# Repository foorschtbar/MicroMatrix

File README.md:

#  MicroMatrix

A very tiny 8x8 Pixel LED Matrix (20x20mm) with 64x SK6805-EC15 (1.5x1.5mm) LEDs. With four panels in a chain (8x32 Pixel) perfect for the [PixelIt](https://github.com/o0shojo0o/PixelIt) project.

### PCB Ordering

:point_up: I still have a few PCBs left. If you are interested please contact me. Contact details can be found here: https://github.com/foorschtbar or visit my Tindie store: 

## Layout

```
00 01 02 03 04 05 06 07

15 14 13 12 11 10 09 08

16 17 18 19 20 21 22 23

31 30 29 28 27 26 25 24

32 33 34 35 36 37 38 39

47 46 45 44 43 42 41 40

48 49 50 51 52 53 54 55

63 62 61 60 59 58 57 56
```
## BOM

See [iBOM](./fab/ibom.html)
## Production and Assembly

1. Open KiCad Command Prompt
2. Panelize PCB with [KiKit](https://github.com/yaqwsx/KiKit)

    `kikit panelize -p kikit_panelize.json MicroMatrix.kicad_pcb MicroMatrix_Panel.kicad_pcb`

3. Build fabrication files (Gerber, BOM, POS)

    `kikit fab jlcpcb --no-drc --assembly --field "LCSC Part Number" --schematic MicroMatrix.kicad_sch MicroMatrix_Panel.kicad_pcb fab`

## Other

Inspired by [gumslone/led-matrix](https://oshwlab.com/gumslone/led-matrix).

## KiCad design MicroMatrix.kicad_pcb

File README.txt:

# SK6805EC15 Matrix

https://oshwlab.com/gumslone/led-matrix

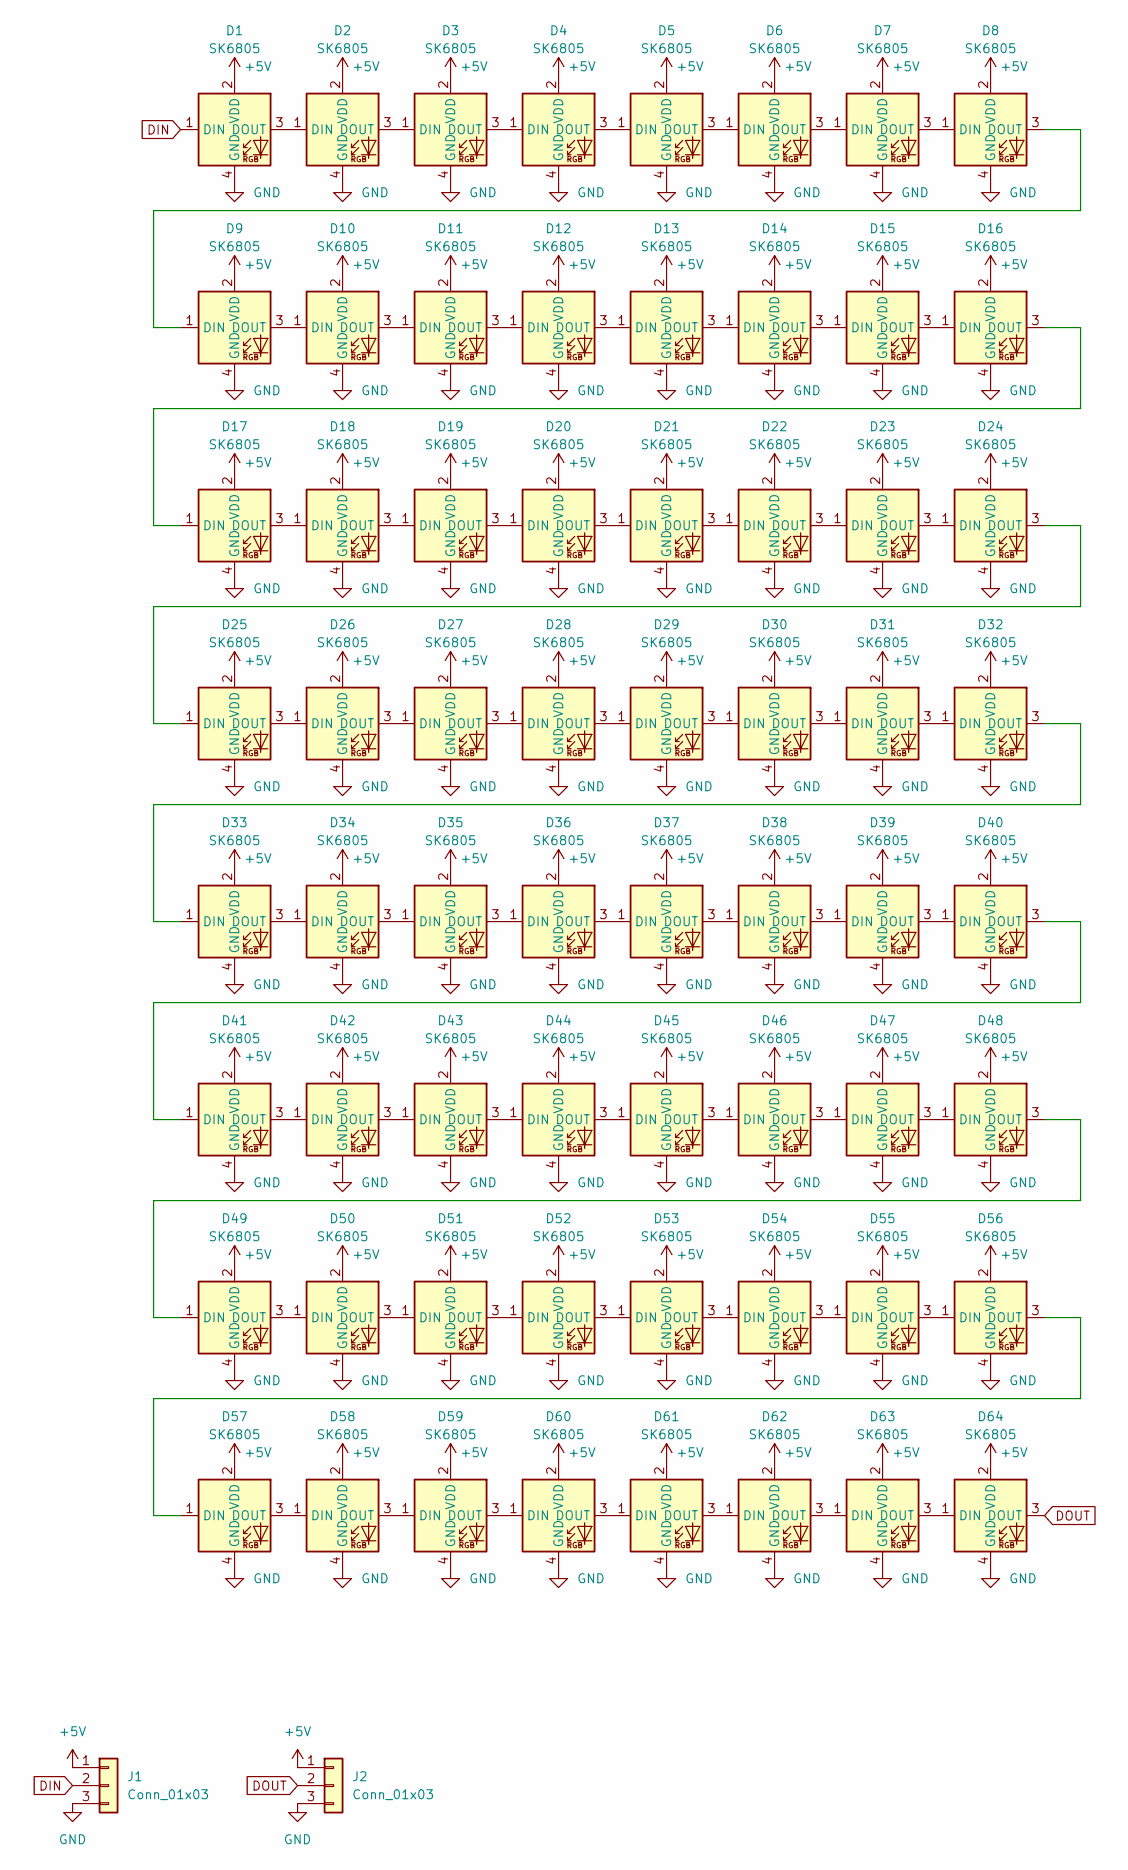
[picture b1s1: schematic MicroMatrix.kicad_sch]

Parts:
D1, D2, D3, D4, D5, D6, D7, D8, D9, D10, D11, D12, D13, D14, D15, D16, D17, D18, D19, D20, D21, D22, D23, D24, D25, D26, D27, D28, D29, D30, D31, D32, D33, D34, D35, D36, D37, D38, D39, D40, D41, D42, D43, D44, D45, D46, D47, D48, D49, D50, D51, D52, D53, D54, D55, D56, D57, D58, D59, D60, D61, D62, D63, D64: SK6805; SK6805-EC15; LCSC Part Number C2890035
J1, J2: Conn_01x03

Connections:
+5V: D1.2 (VDD), D2.2 (VDD), D3.2 (VDD), D4.2 (VDD), D5.2 (VDD), D6.2 (VDD), D7.2 (VDD), D8.2 (VDD), D9.2 (VDD), D10.2 (VDD), D11.2 (VDD), D12.2 (VDD), D13.2 (VDD), D14.2 (VDD), D15.2 (VDD), D16.2 (VDD), D17.2 (VDD), D18.2 (VDD), D19.2 (VDD), D20.2 (VDD), D21.2 (VDD), D22.2 (VDD), D23.2 (VDD), D24.2 (VDD), D25.2 (VDD), D26.2 (VDD), D27.2 (VDD), D28.2 (VDD), D29.2 (VDD), D30.2 (VDD), D31.2 (VDD), D32.2 (VDD), D33.2 (VDD), D34.2 (VDD), D35.2 (VDD), D36.2 (VDD), D37.2 (VDD), D38.2 (VDD), D39.2 (VDD), D40.2 (VDD), D41.2 (VDD), D42.2 (VDD), D43.2 (VDD), D44.2 (VDD), D45.2 (VDD), D46.2 (VDD), D47.2 (VDD), D48.2 (VDD), D49.2 (VDD), D50.2 (VDD), D51.2 (VDD), D52.2 (VDD), D53.2 (VDD), D54.2 (VDD), D55.2 (VDD), D56.2 (VDD), D57.2 (VDD), D58.2 (VDD), D59.2 (VDD), D60.2 (VDD), D61.2 (VDD), D62.2 (VDD), D63.2 (VDD), D64.2 (VDD), J1.1, J2.1
DIN: D1.1 (DIN), J1.2
DOUT: D64.3 (DOUT), J2.2
GND: D1.4 (GND), D2.4 (GND), D3.4 (GND), D4.4 (GND), D5.4 (GND), D6.4 (GND), D7.4 (GND), D8.4 (GND), D9.4 (GND), D10.4 (GND), D11.4 (GND), D12.4 (GND), D13.4 (GND), D14.4 (GND), D15.4 (GND), D16.4 (GND), D17.4 (GND), D18.4 (GND), D19.4 (GND), D20.4 (GND), D21.4 (GND), D22.4 (GND), D23.4 (GND), D24.4 (GND), D25.4 (GND), D26.4 (GND), D27.4 (GND), D28.4 (GND), D29.4 (GND), D30.4 (GND), D31.4 (GND), D32.4 (GND), D33.4 (GND), D34.4 (GND), D35.4 (GND), D36.4 (GND), D37.4 (GND), D38.4 (GND), D39.4 (GND), D40.4 (GND), D41.4 (GND), D42.4 (GND), D43.4 (GND), D44.4 (GND), D45.4 (GND), D46.4 (GND), D47.4 (GND), D48.4 (GND), D49.4 (GND), D50.4 (GND), D51.4 (GND), D52.4 (GND), D53.4 (GND), D54.4 (GND), D55.4 (GND), D56.4 (GND), D57.4 (GND), D58.4 (GND), D59.4 (GND), D60.4 (GND), D61.4 (GND), D62.4 (GND), D63.4 (GND), D64.4 (GND), J1.3, J2.3
unnamed: D1.3 (DOUT), D2.1 (DIN)
unnamed: D2.3 (DOUT), D3.1 (DIN)
unnamed: D3.3 (DOUT), D4.1 (DIN)
unnamed: D4.3 (DOUT), D5.1 (DIN)
unnamed: D5.3 (DOUT), D6.1 (DIN)
unnamed: D6.3 (DOUT), D7.1 (DIN)
unnamed: D7.3 (DOUT), D8.1 (DIN)
unnamed: D8.3 (DOUT), D9.1 (DIN)
unnamed: D9.3 (DOUT), D10.1 (DIN)
unnamed: D10.3 (DOUT), D11.1 (DIN)
unnamed: D11.3 (DOUT), D12.1 (DIN)
unnamed: D12.3 (DOUT), D13.1 (DIN)
unnamed: D13.3 (DOUT), D14.1 (DIN)
unnamed: D14.3 (DOUT), D15.1 (DIN)
unnamed: D15.3 (DOUT), D16.1 (DIN)
unnamed: D16.3 (DOUT), D17.1 (DIN)
unnamed: D17.3 (DOUT), D18.1 (DIN)
unnamed: D18.3 (DOUT), D19.1 (DIN)
unnamed: D19.3 (DOUT), D20.1 (DIN)
unnamed: D20.3 (DOUT), D21.1 (DIN)
unnamed: D21.3 (DOUT), D22.1 (DIN)
unnamed: D22.3 (DOUT), D23.1 (DIN)
unnamed: D23.3 (DOUT), D24.1 (DIN)
unnamed: D24.3 (DOUT), D25.1 (DIN)
unnamed: D25.3 (DOUT), D26.1 (DIN)
unnamed: D26.3 (DOUT), D27.1 (DIN)
unnamed: D27.3 (DOUT), D28.1 (DIN)
unnamed: D28.3 (DOUT), D29.1 (DIN)
unnamed: D29.3 (DOUT), D30.1 (DIN)
unnamed: D30.3 (DOUT), D31.1 (DIN)
unnamed: D31.3 (DOUT), D32.1 (DIN)
unnamed: D32.3 (DOUT), D33.1 (DIN)
unnamed: D33.3 (DOUT), D34.1 (DIN)
unnamed: D34.3 (DOUT), D35.1 (DIN)
unnamed: D35.3 (DOUT), D36.1 (DIN)
unnamed: D36.3 (DOUT), D37.1 (DIN)
unnamed: D37.3 (DOUT), D38.1 (DIN)
unnamed: D38.3 (DOUT), D39.1 (DIN)
unnamed: D39.3 (DOUT), D40.1 (DIN)
unnamed: D40.3 (DOUT), D41.1 (DIN)
unnamed: D41.3 (DOUT), D42.1 (DIN)
unnamed: D42.3 (DOUT), D43.1 (DIN)
unnamed: D43.3 (DOUT), D44.1 (DIN)
unnamed: D44.3 (DOUT), D45.1 (DIN)
unnamed: D45.3 (DOUT), D46.1 (DIN)
unnamed: D46.3 (DOUT), D47.1 (DIN)
unnamed: D47.3 (DOUT), D48.1 (DIN)
unnamed: D48.3 (DOUT), D49.1 (DIN)
unnamed: D49.3 (DOUT), D50.1 (DIN)
unnamed: D50.3 (DOUT), D51.1 (DIN)
unnamed: D51.3 (DOUT), D52.1 (DIN)
unnamed: D52.3 (DOUT), D53.1 (DIN)
unnamed: D53.3 (DOUT), D54.1 (DIN)
unnamed: D54.3 (DOUT), D55.1 (DIN)
unnamed: D55.3 (DOUT), D56.1 (DIN)
unnamed: D56.3 (DOUT), D57.1 (DIN)
unnamed: D57.3 (DOUT), D58.1 (DIN)
unnamed: D58.3 (DOUT), D59.1 (DIN)
unnamed: D59.3 (DOUT), D60.1 (DIN)
unnamed: D60.3 (DOUT), D61.1 (DIN)
unnamed: D61.3 (DOUT), D62.1 (DIN)
unnamed: D62.3 (DOUT), D63.1 (DIN)
unnamed: D63.3 (DOUT), D64.1 (DIN)

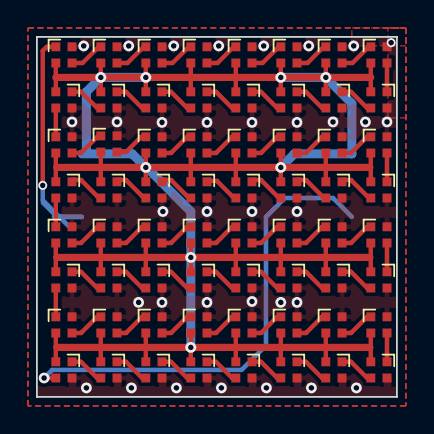
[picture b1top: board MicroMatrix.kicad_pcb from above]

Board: 2 copper layers, 20.0 x 20.0 mm, 64 parts (0 on the bottom side), 65 nets.

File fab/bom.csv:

Comment,Designator,Footprint,LCSC
SK6805,"D1,D2,D3,D4,D5,D6,D7,D8,D9,D10,D11,D12,D13,D14,D15,D16,D17,D18,D19,D20,D21,D22,D23,D24,D25,D26,D27,D28,D29,D30,D31,D32,D33,D34,D35,D36,D37,D38,D39,D40,D41,D42,D43,D44,D45,D46,D47,D48,D49,D50,D51,D52,D53,D54,D55,D56,D57,D58,D59,D60,D61,D62,D63,D64",LED_SMD:LED_SK6812_EC15_1.5x1.5mm,C2890035

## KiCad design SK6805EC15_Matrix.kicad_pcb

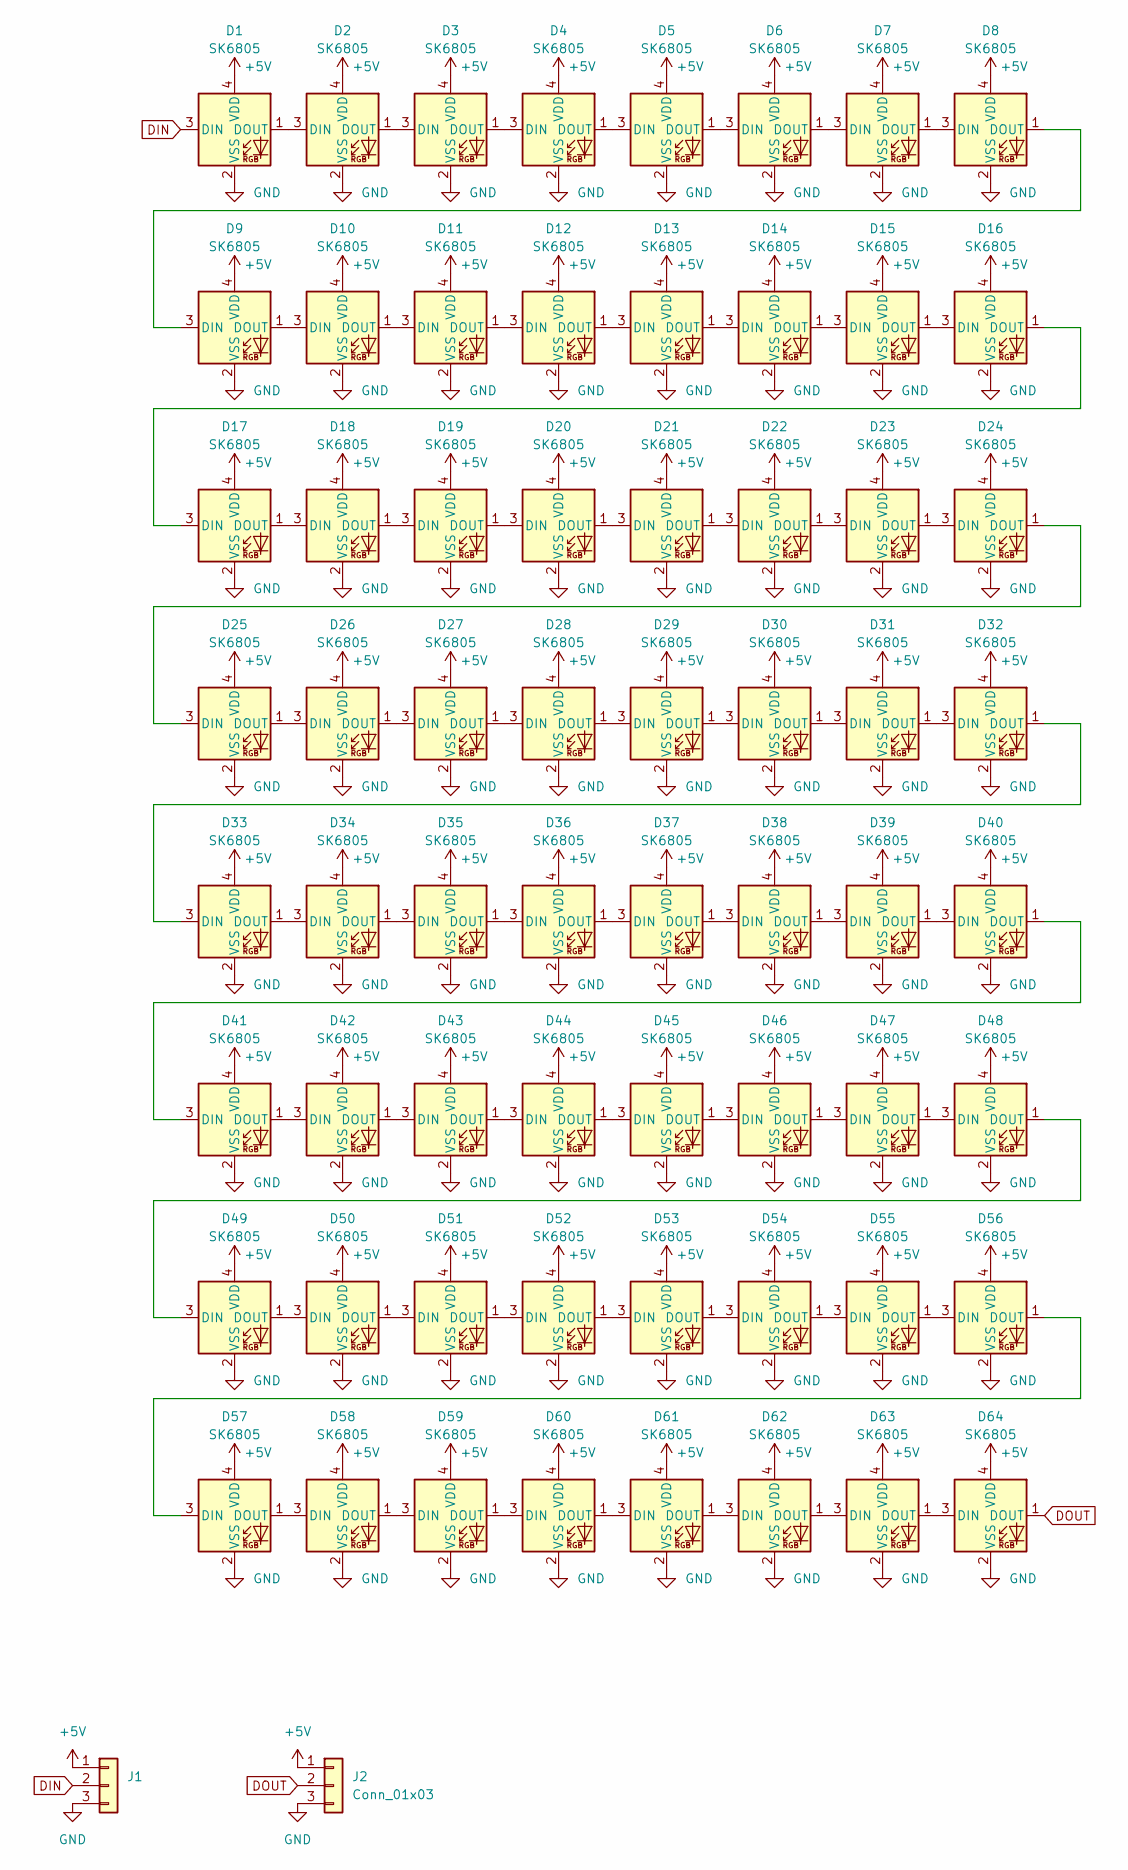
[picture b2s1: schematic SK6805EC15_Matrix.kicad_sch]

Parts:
D1, D2, D3, D4, D5, D6, D7, D8, D9, D10, D11, D12, D13, D14, D15, D16, D17, D18, D19, D20, D21, D22, D23, D24, D25, D26, D27, D28, D29, D30, D31, D32, D33, D34, D35, D36, D37, D38, D39, D40, D41, D42, D43, D44, D45, D46, D47, D48, D49, D50, D51, D52, D53, D54, D55, D56, D57, D58, D59, D60, D61, D62, D63, D64: SK6805; LED_SK6812_EC15_1.5x1.5mm
J1: (no value)
J2: Conn_01x03

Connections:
+5V: D1.4 (VDD), D2.4 (VDD), D3.4 (VDD), D4.4 (VDD), D5.4 (VDD), D6.4 (VDD), D7.4 (VDD), D8.4 (VDD), D9.4 (VDD), D10.4 (VDD), D11.4 (VDD), D12.4 (VDD), D13.4 (VDD), D14.4 (VDD), D15.4 (VDD), D16.4 (VDD), D17.4 (VDD), D18.4 (VDD), D19.4 (VDD), D20.4 (VDD), D21.4 (VDD), D22.4 (VDD), D23.4 (VDD), D24.4 (VDD), D25.4 (VDD), D26.4 (VDD), D27.4 (VDD), D28.4 (VDD), D29.4 (VDD), D30.4 (VDD), D31.4 (VDD), D32.4 (VDD), D33.4 (VDD), D34.4 (VDD), D35.4 (VDD), D36.4 (VDD), D37.4 (VDD), D38.4 (VDD), D39.4 (VDD), D40.4 (VDD), D41.4 (VDD), D42.4 (VDD), D43.4 (VDD), D44.4 (VDD), D45.4 (VDD), D46.4 (VDD), D47.4 (VDD), D48.4 (VDD), D49.4 (VDD), D50.4 (VDD), D51.4 (VDD), D52.4 (VDD), D53.4 (VDD), D54.4 (VDD), D55.4 (VDD), D56.4 (VDD), D57.4 (VDD), D58.4 (VDD), D59.4 (VDD), D60.4 (VDD), D61.4 (VDD), D62.4 (VDD), D63.4 (VDD), D64.4 (VDD), J1.1, J2.1
DIN: D1.3 (DIN), J1.2
DOUT: D64.1 (DOUT), J2.2
GND: D1.2 (VSS), D2.2 (VSS), D3.2 (VSS), D4.2 (VSS), D5.2 (VSS), D6.2 (VSS), D7.2 (VSS), D8.2 (VSS), D9.2 (VSS), D10.2 (VSS), D11.2 (VSS), D12.2 (VSS), D13.2 (VSS), D14.2 (VSS), D15.2 (VSS), D16.2 (VSS), D17.2 (VSS), D18.2 (VSS), D19.2 (VSS), D20.2 (VSS), D21.2 (VSS), D22.2 (VSS), D23.2 (VSS), D24.2 (VSS), D25.2 (VSS), D26.2 (VSS), D27.2 (VSS), D28.2 (VSS), D29.2 (VSS), D30.2 (VSS), D31.2 (VSS), D32.2 (VSS), D33.2 (VSS), D34.2 (VSS), D35.2 (VSS), D36.2 (VSS), D37.2 (VSS), D38.2 (VSS), D39.2 (VSS), D40.2 (VSS), D41.2 (VSS), D42.2 (VSS), D43.2 (VSS), D44.2 (VSS), D45.2 (VSS), D46.2 (VSS), D47.2 (VSS), D48.2 (VSS), D49.2 (VSS), D50.2 (VSS), D51.2 (VSS), D52.2 (VSS), D53.2 (VSS), D54.2 (VSS), D55.2 (VSS), D56.2 (VSS), D57.2 (VSS), D58.2 (VSS), D59.2 (VSS), D60.2 (VSS), D61.2 (VSS), D62.2 (VSS), D63.2 (VSS), D64.2 (VSS), J1.3, J2.3
unnamed: D1.1 (DOUT), D2.3 (DIN)
unnamed: D2.1 (DOUT), D3.3 (DIN)
unnamed: D3.1 (DOUT), D4.3 (DIN)
unnamed: D4.1 (DOUT), D5.3 (DIN)
unnamed: D5.1 (DOUT), D6.3 (DIN)
unnamed: D6.1 (DOUT), D7.3 (DIN)
unnamed: D7.1 (DOUT), D8.3 (DIN)
unnamed: D8.1 (DOUT), D9.3 (DIN)
unnamed: D10.1 (DOUT), D11.3 (DIN)
unnamed: D9.1 (DOUT), D10.3 (DIN)
unnamed: D11.1 (DOUT), D12.3 (DIN)
unnamed: D12.1 (DOUT), D13.3 (DIN)
unnamed: D13.1 (DOUT), D14.3 (DIN)
unnamed: D14.1 (DOUT), D15.3 (DIN)
unnamed: D15.1 (DOUT), D16.3 (DIN)
unnamed: D16.1 (DOUT), D17.3 (DIN)
unnamed: D17.1 (DOUT), D18.3 (DIN)
unnamed: D18.1 (DOUT), D19.3 (DIN)
unnamed: D19.1 (DOUT), D20.3 (DIN)
unnamed: D20.1 (DOUT), D21.3 (DIN)
unnamed: D21.1 (DOUT), D22.3 (DIN)
unnamed: D22.1 (DOUT), D23.3 (DIN)
unnamed: D23.1 (DOUT), D24.3 (DIN)
unnamed: D24.1 (DOUT), D25.3 (DIN)
unnamed: D25.1 (DOUT), D26.3 (DIN)
unnamed: D26.1 (DOUT), D27.3 (DIN)
unnamed: D27.1 (DOUT), D28.3 (DIN)
unnamed: D28.1 (DOUT), D29.3 (DIN)
unnamed: D29.1 (DOUT), D30.3 (DIN)
unnamed: D30.1 (DOUT), D31.3 (DIN)
unnamed: D31.1 (DOUT), D32.3 (DIN)
unnamed: D32.1 (DOUT), D33.3 (DIN)
unnamed: D33.1 (DOUT), D34.3 (DIN)
unnamed: D34.1 (DOUT), D35.3 (DIN)
unnamed: D35.1 (DOUT), D36.3 (DIN)
unnamed: D36.1 (DOUT), D37.3 (DIN)
unnamed: D37.1 (DOUT), D38.3 (DIN)
unnamed: D38.1 (DOUT), D39.3 (DIN)
unnamed: D39.1 (DOUT), D40.3 (DIN)
unnamed: D40.1 (DOUT), D41.3 (DIN)
unnamed: D41.1 (DOUT), D42.3 (DIN)
unnamed: D42.1 (DOUT), D43.3 (DIN)
unnamed: D43.1 (DOUT), D44.3 (DIN)
unnamed: D44.1 (DOUT), D45.3 (DIN)
unnamed: D45.1 (DOUT), D46.3 (DIN)
unnamed: D46.1 (DOUT), D47.3 (DIN)
unnamed: D47.1 (DOUT), D48.3 (DIN)
unnamed: D48.1 (DOUT), D49.3 (DIN)
unnamed: D49.1 (DOUT), D50.3 (DIN)
unnamed: D50.1 (DOUT), D51.3 (DIN)
unnamed: D51.1 (DOUT), D52.3 (DIN)
unnamed: D52.1 (DOUT), D53.3 (DIN)
unnamed: D53.1 (DOUT), D54.3 (DIN)
unnamed: D54.1 (DOUT), D55.3 (DIN)
unnamed: D55.1 (DOUT), D56.3 (DIN)
unnamed: D56.1 (DOUT), D57.3 (DIN)
unnamed: D57.1 (DOUT), D58.3 (DIN)
unnamed: D58.1 (DOUT), D59.3 (DIN)
unnamed: D59.1 (DOUT), D60.3 (DIN)
unnamed: D60.1 (DOUT), D61.3 (DIN)
unnamed: D61.1 (DOUT), D62.3 (DIN)
unnamed: D62.1 (DOUT), D63.3 (DIN)
unnamed: D63.1 (DOUT), D64.3 (DIN)

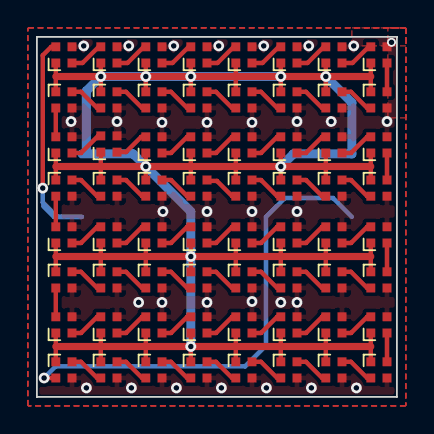
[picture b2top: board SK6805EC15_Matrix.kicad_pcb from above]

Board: 2 copper layers, 20.0 x 20.0 mm, 64 parts (0 on the bottom side), 65 nets.

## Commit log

2022-05-24 Inital commit
2022-05-24 Finished PCB front
2022-05-24 Finished PCB Back
2022-05-24 Added Datasheet
2022-05-24 Optimized PCB and added silkscreen
2022-05-26 Small enhancments
2022-05-26 Renamed project
2022-06-05 Added Gerber files
2022-06-05 Fixed README
2022-06-05 Added demo GIF
2022-06-09 Fixed typo
2022-06-09 Added BOM
2022-06-10 Removed Gerber dir
2022-06-10 Added images
2022-06-10 Moved Datasheet
2022-06-10 Renamed project to MicroMatrix
2022-06-10 Added KiKit Panelizer
2022-06-14 Updated panel settings for fab
2022-06-17 Added 3D Model for LED
2022-06-17 Simplifyed KiKat 3D Model
2022-06-17 Fixed the 3rd row postion (0.1mm)
2022-06-17 Added panel rendering to README
2022-06-19 Updated Panel PCB to REV1.2
2022-06-19 Updated iBOM to REV1.2
2022-06-20 Fixed Trace in REV1.2
2024-01-09 Added correct SK6805-EC15 Footprint and Symbol
2024-01-09 Updated PCB to REV1.3 Replaced SK6805 footprint/symbol with a own version
2024-01-09 Updated production files
2024-04-20 Added Tindie store link
2024-04-27 Updated ibom

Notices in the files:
MicroMatrix.kicad_pcb:
© foorschtbar
